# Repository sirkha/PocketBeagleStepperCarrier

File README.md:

# PocketBeagleStepperCarrier
A board that utilizes a PocketBeagle to control stepper motors via Pololu like carriers.

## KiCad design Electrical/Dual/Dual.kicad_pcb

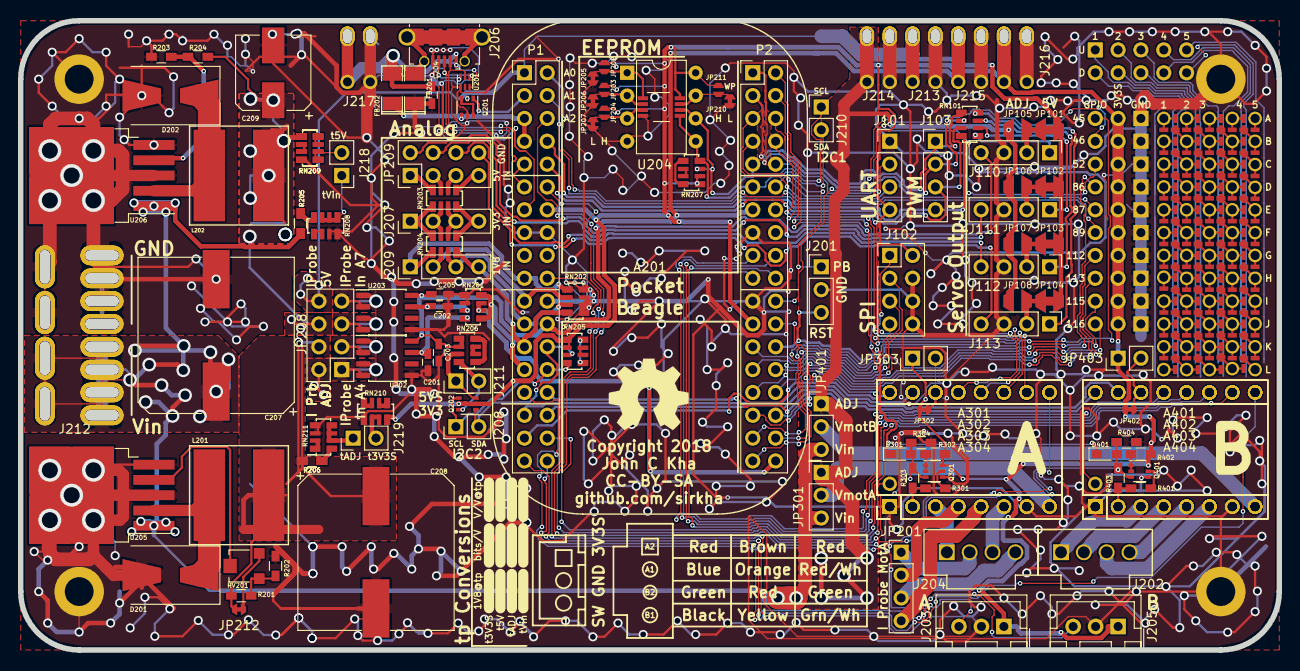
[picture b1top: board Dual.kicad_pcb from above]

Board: 2 copper layers, 140.0 x 70.0 mm, 192 parts (1 on the bottom side), 154 nets.

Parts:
A201: PocketBeagle
A301, A401: Pololu_Breakout_A4988; Pololu_Breakout-16_15.2x20.3mm
A302, A402: Pololu_Breakout_DRV8825; Pololu_Breakout-16_15.2x20.3mm
A303, A403: Pololu_Breakout_DRV8834; Pololu_Breakout-16_15.2x20.3mm
A304, A404: Pololu_Breakout_DRV8880; Pololu_Breakout-17_15.2x20.3mm
C201, C202: 1nF; C_0603_HandSoldering
C203, C204, C205: 100nF; C_0603_HandSoldering
C207, C208: 1000uF; CP_Elec_17x17
C209: 1000uF; CP_Elec_8x10
D201, D202: SK34A; D_SMB-SMC_Universal_Handsoldering
D301, D401: D; D_0603_HandSoldering
FB201, FB202: 120; SMD-1206_Pol
J101, J103, J110, J111, J112, J113, J207, J209: 01x04; Pin_Header_Straight_1x04_Pitch2.54mm
J102: 02x04; Pin_Header_Straight_2x04_Pitch2.54mm
J104, J105, J106, J107, J108, J109, J114, J115, J116, J117: 01x03; Pin_Header_Straight_1x03_Pitch2.54mm_Blank
J201: 01x03; Pin_Header_Straight_1x03_Pitch2.54mm
J202, J204: 01x04; Molex-SL-4POS
J203, J205: 01x03; JST_XH_B03B-XH-A_03x2.50mm_Straight
J206: USB_OTG; USB_Micro-B_Molex-105017-0001_CircularHoles
J208, J210, J211, J218, J219: 01x02; Pin_Header_Straight_1x02_Pitch2.54mm
J212: 4PostTerm; TerminalBlock_Custom_1x04P5.08mm
J213, J214, J215, J216, J217: 2PostTerm; TerminalBlock_Custom_1x02.54mm
JP101, JP102, JP103, JP104: JPNC; JPNC_Large
JP105, JP106, JP107, JP108: JPNO; JPNO_Large
JP201: 01x04; Pin_Header_Straight_1x04_Pitch2.54mm
JP202, JP203, JP204, JP211: JPNO
JP205, JP206, JP207, JP210, JP212, JP302, JP402: JPNC
JP208, JP209: 02x04; Pin_Header_Straight_2x04_Pitch2.54mm_AB
JP301, JP401: 01x03; Pin_Header_Straight_1x03_Pitch2.54mm
JP303, JP403: 01x02; Pin_Header_Straight_1x02_Pitch2.54mm
L201, L202: 100uH; BOURNS-SRN1060
MK201, MK202, MK203, MK204: Mounting_Hole_PAD; MountingHole_3.2mm_M3_ISO14580_Pad
Q201, Q301, Q401: FDC6420C; SOT-363_SC-70-6
Q202: FDG1024NZ; SOT-363_SC-70-6
R201: Rsel; R_0603_HandSoldering
R202, R303, R403: 1K2; R_0603_HandSoldering
R203: 3.9K; R_0603_HandSoldering
R204, R205, R205#2, R206, R206#2, R302, R304, R402, R404: 12K; R_0603_HandSoldering
R301, R401: 22; R_0603_HandSoldering
RN101, RN201, RN202, RN203, RN204, RN205, RN206, RN207, RN208, RN209, RN209#2, RN210, RN211: 1K2; R_Array_1206x04
RV201: 50K; Potentiometer_Trimmer-EVM3E
U201: TPD4S012; WSON6_1.5x1.5mm_Pitch0.5mm
U202, U203: ACS723LLCTR-05AB-T; SOIC-8_3.9x4.9mm_Pitch1.27mm
U204: 24LC256; Dip-MSOP-8
U205, U206: LM2576HVS-ADJ; TO-263-5_TabPin3
x100: 02x05; Pin_Header_Straight_2x05_Pitch2.54mm
x101, x113, x125, x137: RoutaCell; RoutaCellTop
x102, x103, x104, x105, x106, x107, x108, x109, x110, x111: RoutaCell; RoutaCellLeft
x112: RoutaCell; RoutaCellBottomLeft
x114, x115, x116, x117, x118, x119, x120, x121, x122, x123, x126, x127, x128, x129, x130, x131, x132, x133, x134, x135, x138, x139, x140, x141, x142, x143, x144, x145, x146, x147: RoutaCell
x124, x136, x148: RoutaCell; RoutaCellBottom
x149: RoutaCell; RoutaCellTopRight
x150, x151, x152, x153, x154, x155, x156, x157, x158, x159: RoutaCell; RoutaCellRight
x160: RoutaCell; RoutaCellBottomRight

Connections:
3V3S: A201.1.14, A201.2.23, J101.4, J102.2, J104.2, J105.2, J106.2, J107.2, J108.2, J109.2, J114.2, J115.2, J116.2, J117.2, J203.1, J205.1, J216.1, JP202.1, JP203.1, JP204.1, JP211.2, JP302.2, JP303.1, JP402.2, JP403.1, Q202.2, Q202.5, Q301.6, Q401.6, R302.1, R402.1, RN205.1, RN205.2, RN207.5, RN207.6, RN210.8, U204.8
5VS: A201.1.24, A201.2.13, C203.1, C205.1, J215.1, RN206.1, RN206.2, U202.8, U203.8
+5V: A201.1.1, J213.1, JP101.1, JP102.1, JP103.1, JP104.1, JP208.b4, Q201.2
/Common/IP_5V: C209.1, JP208.b3, L202.2, R204.1, RN209.1, RN209#2.1
/Common/IP_vadj: C208.1, JP208.b2, JP212.2, L201.2, R201.1, R206.2, R206#2.2
/Common/StepperA/A1: A301.4, A302.4, A303.4, A304.4, JP201.2
/Common/StepperA/A2: A301.3, A302.3, A303.3, A304.3, J204.1
/Common/StepperA/B1: A301.5, A302.5, A303.5, A304.5, JP201.4
/Common/StepperA/B2: A301.6, A302.6, A303.6, A304.6, J204.3
/Common/StepperA/SLP: A301.14, A302.14, A303.14, A304.14, JP302.1, JP303.2
/Common/StepperA/Vmot: A301.8, A302.8, A303.8, A304.8, JP301.2
/Common/StepperA/fault_supply: A301.2, A302.2, A303.2, A304.2, R301.1, R303.2
/Common/StepperB/A1: A401.4, A402.4, A403.4, A404.4, J202.2
/Common/StepperB/A2: A401.3, A402.3, A403.3, A404.3, J202.1
/Common/StepperB/B1: A401.5, A402.5, A403.5, A404.5, J202.4
/Common/StepperB/B2: A401.6, A402.6, A403.6, A404.6, J202.3
/Common/StepperB/SLP: A401.14, A402.14, A403.14, A404.14, JP402.1, JP403.2
/Common/StepperB/Vmot: A401.8, A402.8, A403.8, A404.8, JP401.2
/Common/StepperB/fault_supply: A401.2, A402.2, A403.2, A404.2, R401.1, R403.2
/Common/ain0: A201.1.19, J209.1, RN202.1, RN204.1
/Common/ain1: A201.1.21, J209.2, RN202.2, RN204.2
/Common/ain2: A201.1.23, J209.3, RN202.3, RN204.3
/Common/ain3: A201.1.25, J209.4, RN202.4, RN204.4
/Common/ain4: A201.1.27, RN201.1, RN201.4
/Common/ain7: A201.2.36, RN201.2, RN201.3
/Common/gpio0_4: A201.1.12, D401.2, Q401.3, R403.1, R404.1
/Common/gpio0_5: A201.1.6, D301.2, Q301.3, R303.1, R304.1
/Common/gpio0_26: A201.1.34, A304.17
/Common/gpio0_27: A201.2.19, A401.11, A402.11, A403.11, A404.11
/Common/gpio1_12: A201.2.24, A404.17
/Common/gpio1_15: A201.2.18, A401.12, A402.12, A403.12, A404.12
/Common/gpio1_25: A201.2.6, A301.12, A302.12, A303.12, A304.12
/Common/gpio1_26: A201.2.4, A301.11, A302.11, A303.11, A304.11
/Common/gpio1_27: A201.2.2, A301.10, A302.10, A303.10, A304.10
/Common/gpio1_28: A201.2.8, A301.13, A302.13, A303.13, A304.13
/Common/gpio2_0: A201.2.20, A401.10, A402.10, A403.10, A404.10
/Common/gpio2_1: A201.2.17, A401.13, A402.13, A403.13, A404.13
/Common/i2c1_scl: A201.2.9, J210.1, RN207.7, U204.6
/Common/i2c1_sda: A201.2.11, J210.2, RN207.8, U204.5
/Common/i2c2_scl: A201.1.28, J208.1, Q202.1, RN205.4
/Common/i2c2_sda: A201.1.26, J208.2, Q202.4, RN205.3
/Common/pr1_pru0_pru_r30_00: A201.1.36, A401.9, A402.9, A403.9, A404.9
/Common/pr1_pru0_pru_r30_01: A201.1.33, A301.16, A302.16, A303.16, A304.16
/Common/pr1_pru0_pru_r30_04: A201.1.31, A301.15, A302.15, A303.15, A304.15
/Common/pr1_pru0_pru_r30_07: A201.1.29, A301.9, A302.9, A303.9, A304.9
/Common/pr1_pru0_pru_r31_16: A201.1.20, J205.3
/Common/pr1_pru1_pru_r30_14: A201.1.32, A401.15, A402.15, A403.15, A404.15
/Common/pr1_pru1_pru_r30_15: A201.1.30, A401.16, A402.16, A403.16, A404.16
/Common/pr1_pru1_pru_r31_10: A201.1.35, J203.3
/Common/usb1_5V: C204.1, FB202.2, J206.1, J217.1, U201.6
/Common/usb1_d+: A201.1.11, J206.3, U201.1
/Common/usb1_d-: A201.1.9, J206.2, U201.2
/Common/usb1_drvvbus: A201.1.3, Q201.1
/Common/usb1_id: A201.1.13, J206.4, U201.3
/Common/usb1_vbus: A201.1.5, A201.1.7, FB202.1, Q201.4
/ain_0: J110.4, JP209.b1
/ain_1: J111.4, JP209.b2
/ain_2: J112.4, JP209.b3
/ain_3: J113.4, JP209.b4
/ehrpwm0A: A201.1.8, J103.4, RN101.4
/ehrpwm0B: A201.1.10, J103.3, RN101.3
/ehrpwm1A: A201.2.1, J103.2, RN101.2
/ehrpwm2B: A201.2.3, J103.1, RN101.1
/gpio1_13: A201.2.33, J104.3
/gpio1_14: A201.2.22, J105.3
/gpio1_20: A201.2.10, J106.3
/gpio2_22: A201.2.35, J107.3
/gpio2_23: A201.1.2, J108.3
/gpio2_25: A201.1.4, J109.3
/gpio3_16: A201.2.32, J114.3
/gpio3_17: A201.2.30, J115.3
/gpio3_19: A201.2.34, J116.3
/gpio3_20: A201.2.28, J117.3
/spi1_cs1: A201.2.31, J102.3
/spi1_d0: A201.2.27, J102.7
/spi1_d1: A201.2.25, J102.1
/spi1_sclk: A201.2.29, J102.5
/uart4_rxd: A201.2.5, J101.3
/uart4_txd: A201.2.7, J101.2
GND: A201.1.15, A201.1.16, A201.1.22, A201.2.15, A201.2.21, A301.1, A301.7, A302.1, A302.7, A303.1, A303.7, A304.1, A304.7, A401.1, A401.7, A402.1, A402.7, A403.1, A403.7, A404.1, A404.7, C201.2, C202.2, C203.2, C204.2, C205.2, C207.2, C208.2, C209.2, D201.2, D202.2, FB201.1, J101.1, J102.4, J102.6, J102.8, J104.1, J105.1, J106.1, J107.1, J108.1, J109.1, J110.3, J111.3, J112.3, J113.3, J114.1, J115.1, J116.1, J117.1, J201.2, J203.2, J205.2, J206.5, J212.1, J212.2, J213.2, J214.2, J215.2, J216.2, J217.2, JP205.1, JP206.1, JP207.1, JP210.1, MK201.1, MK202.1, MK203.1, MK204.1, Q201.5, Q301.4, Q401.4, R202.1, R203.1, R304.2, R404.2, RN201.5, RN201.6, RN202.5, RN202.6, RN202.7, RN202.8, RN208.3, RN208.4, RN209.4, RN209#2.4, RN210.5, RN211.5, RN211.6, U201.4, U202.5, U203.5, U204.4, U205.3, U205.5, U206.3, U206.5
unnamed: A201.2.12, J201.1
unnamed: C201.1, RN201.8, U202.7
unnamed: C202.1, RN201.7, U203.7
unnamed: D201.1, L201.1, U205.2
unnamed: D202.1, L202.1, U206.2
unnamed: FB201.2, J206.6
unnamed: J110.1, RN101.5
unnamed: J110.2, JP101.2, JP105.1
unnamed: J111.1, RN101.6
unnamed: J111.2, JP102.2, JP106.1
unnamed: J112.1, RN101.7
unnamed: J112.2, JP103.2, JP107.1
unnamed: J113.1, RN101.8
unnamed: J113.2, JP104.2, JP108.1
unnamed: J204.2, JP201.1
unnamed: J204.4, JP201.3
unnamed: J207.1, RN203.1, RN204.8
unnamed: J207.2, RN203.2, RN204.7
unnamed: J207.3, RN203.3, RN204.6
unnamed: J207.4, RN203.4, RN204.5
unnamed: J211.1, Q202.6, RN206.3
unnamed: J211.2, Q202.3, RN206.4
unnamed: J218.1, RN208.5, RN208.6, RN208.7
unnamed: J218.2, RN209.5, RN209.6, RN209#2.5, RN209#2.6
unnamed: J219.1, RN211.2, RN211.3, RN211.4
unnamed: J219.2, RN210.6, RN210.7
unnamed: JP202.2, JP205.2, U204.1
unnamed: JP203.2, JP206.2, U204.2
unnamed: JP204.2, JP207.2, U204.3
unnamed: JP208.a1, U202.3, U202.4
unnamed: JP208.a2, U202.1, U202.2
unnamed: JP208.a3, U203.3, U203.4
unnamed: JP208.a4, U203.1, U203.2
unnamed: JP209.a1, RN203.8
unnamed: JP209.a2, RN203.7
unnamed: JP209.a3, RN203.6
unnamed: JP209.a4, RN203.5
unnamed: JP210.2, JP211.1, U204.7
unnamed: JP212.1, RV201.3
unnamed: Q201.3, Q201.6
unnamed: Q301.1, Q301.2, R302.2
unnamed: Q301.5, R301.2
unnamed: Q401.1, Q401.2, R402.2
unnamed: Q401.5, R401.2
unnamed: R201.2, R202.2, RV201.1
unnamed: R203.2, R204.2, U206.4
unnamed: R205.1, R205#2.1, RN208.8
unnamed: R206.1, R206#2.1, RN211.1
unnamed: RN205.5, RN205.8
unnamed: RN205.6, RN205.7
unnamed: RN206.5, RN206.8
unnamed: RN206.6, RN206.7
unnamed: RN207.1, RN207.4
unnamed: RN207.2, RN207.3
unnamed: RN208.1, RN208.2
unnamed: RN209.2, RN209.3, RN209#2.2, RN209#2.3
unnamed: RN209.7, RN209.8, RN209#2.7, RN209#2.8
unnamed: RN210.1, RN210.2
unnamed: RN210.3, RN210.4
unnamed: RN211.7, RN211.8
unnamed: RV201.2, U205.4
unnamed: x100.1, x101.U, x102.U, x103.U, x104.U, x105.U, x106.U, x107.U, x108.U, x109.U, x110.U, x111.U, x112.U
unnamed: x100.2, x101.D, x102.D, x103.D, x104.D, x105.D, x106.D, x107.D, x108.D, x109.D, x110.D, x111.D, x112.D
unnamed: x100.3, x113.U, x114.U, x115.U, x116.U, x117.U, x118.U, x119.U, x120.U, x121.U, x122.U, x123.U, x124.U
unnamed: x100.4, x113.D, x114.D, x115.D, x116.D, x117.D, x118.D, x119.D, x120.D, x121.D, x122.D, x123.D, x124.D
unnamed: x100.5, x125.U, x126.U, x127.U, x128.U, x129.U, x130.U, x131.U, x132.U, x133.U, x134.U, x135.U, x136.U
unnamed: x100.6, x125.D, x126.D, x127.D, x128.D, x129.D, x130.D, x131.D, x132.D, x133.D, x134.D, x135.D, x136.D
unnamed: x100.7, x137.U, x138.U, x139.U, x140.U, x141.U, x142.U, x143.U, x144.U, x145.U, x146.U, x147.U, x148.U
unnamed: x100.8, x137.D, x138.D, x139.D, x140.D, x141.D, x142.D, x143.D, x144.D, x145.D, x146.D, x147.D, x148.D
unnamed: x100.9, x149.U, x150.U, x151.U, x152.U, x153.U, x154.U, x155.U, x156.U, x157.U, x158.U, x159.U, x160.U
unnamed: x100.10, x149.D, x150.D, x151.D, x152.D, x153.D, x154.D, x155.D, x156.D, x157.D, x158.D, x159.D, x160.D
RST: A201.2.26, D301.1, D401.1, J201.3
Vadj: J214.1, JP105.2, JP106.2, JP107.2, JP108.2, JP208.b1, JP301.1, JP401.1
Vin: C207.1, J212.3, J212.4, JP301.3, JP401.3, R205.2, R205#2.2, U205.1, U206.1

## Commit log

2018-01-10 Added Licensing information
2018-01-10 Modified Kicad modules component library, adding PocketBeagle, Pololu drv8880 and drv8834 boards.
2018-01-10 Added IC component library, currently containing just the FDC6420C N/P-Channel dual MOSFET.
2018-01-10 Used [QUCS-S](https://github.com/ra3xdh/qucs_s) to develop/simulate fault/VDD support for drv/A4988 boards.
2018-01-10 Used QUCS-S to test resistor dividers.
2018-01-10 Application specific circuitry common to quad and dual boards completed. TODO: Common I2C, USB and EEPROM interfaces.
2018-01-11 Fixed Pocketbeagle pin swap (maybe)
2018-01-11 Completed components common to both quad and dual steppers (with the exception of power breakouts)
2018-01-12 Completed Schematic for Dual implementation
2018-01-12 Updated resistor values in simulation.
2018-01-12 Added TPD4S012 4 Channel USB ESD Solution with Power Clamp
2018-01-12 Completed quad schematics
2018-01-12 Fixed DRC errors
2018-01-13 Added Bourns SRN1060 footprint from https://github.com/cpavlina/kicad-pcblib/blob/master/manuf.pretty/BOURNS-SRN1060.kicad_mod
2018-01-13 Added NC pin 5.
2018-01-13 Associated footprints. Added some footprint libraries to support.
2018-01-13 Fixed issues with socket strips vs pin headers
2018-01-13 Added footprints for Quad
2018-01-14 Fixed misnumbered pin 2.21->2.25 for GPIO_41
2018-01-14 Corrected pin 17 and 18 positions
2018-01-14 Small and large solder jumpers. Small for signals, large for power.
2018-01-14 Pin numbers now match symbol.
2018-01-14 Added Molex SL Footprint for stepper motor outputs. Thanks to https://bitbucket.org/alexwarrior/.
2018-01-14 A and B port numbering for 2x4 pin header.
2018-01-14 Blank pin header for GPIO header on dual.
2018-01-14 Edited pad solder mask dimensions and switched to graphic line for pad jumper to avoid DRC errors.
2018-01-15 Text the way I want it in these librarires.
2018-01-15 Working on layout and routing.
2018-01-15 Switched Stepper sheets A and B to improve numbering... hopefully?
2018-01-16 Improved solder jumpers to make mask only extend between pads instead of all around the pad.
2018-01-18 Completed Dual Stepper Layout. TODO: Via stitching.
2018-01-18 Changed thermal relief width.
2018-01-18 Changed thermal relief width and added pads for proper slot fabrication.
2018-01-18 Added routacell like prototyping area.
2018-01-18 Circular holes for proper fab.
2018-01-18 Vias Stitched
2018-01-19 Deleted extranious 3V3S line. Cleaned up tracks as a result.
2018-01-19 Fixed silkscreen error on stepper references.
2018-01-19 Fixed hole sizes and thermal reliefs in libraries and on dual boards.
2018-01-20 Added ground connection to power button/reset header.
2018-01-20 Added a diode to the stepper fault/3v3 supply to ensure fault remains low when RESET/PMIC_OUT_PGOOD is low.
2018-01-21 Switched two pins for easier routing on quad board.
2018-01-21 Completed Quad stepper version of the board.
2018-01-21 fixed unconnected pad 6 on RN201
2018-01-21 Applied improvements from routing quad board to dual board.
2018-01-21 DRC Erros fixed.
2018-01-22 Fixed silkscreen errors and other minor improvements to trace layouts.
2018-01-22 Made pin one consistantly SCL on both sets of I2C headers.
2018-01-23 Used bigger capacitor footprints to allow for 1000 uF electrolytics at 50V
2018-02-03 Changed clearences on JP101-JP108 to prevent ground filling between jumper pads.
2018-02-09 ACS712 -> ACS723
2018-02-09 FB <> Fuse; FB == Ferrite Bead
2018-02-13 Rearranged the power outputs to support TE Connectivity AMP connectors.
2018-02-19 Modified main power input footprint to support other connectors
2018-02-20 Rearranged EEPROM to add an MSOP option and make the address/WP pins more accessible
2018-02-20 Fixed footprint (kicad library is wrong?)
2018-02-27 Modified ground viaing for better soldering.
2019-01-18 Project output updated

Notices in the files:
Electrical/Dual/Dual.kicad_pcb:
Copyright 2018
CC-BY-SA
